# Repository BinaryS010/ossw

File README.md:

# Open SCART SWitch (OSSW)

## Overview

The **Open SCART Switch** (OSSW) is an RGB video and audio SCART switch designed to connect up to **8** RGB capable video game consoles with compatible display devices or scalers such as the **Open Source Scan Converter (OSSC).**

It was designed for use with properly constructed **RGB SCART** cables which correctly attenuate video and sync signals to levels safe for use with consumer grade televisions and the OSSC.

## Motivation

I designed this device to scratch a few itches, but mostly because there are currently no open source SCART switch designs within the retro gaming community.

It would have been cheaper to buy an existing solution, of which there are several very good ones, but I've learnt a lot throughout this project.

## Features

Currently the OSSW has the following features:

 * **8** SCART **inputs**, with **2** SCART **outputs**. Supports simultaneous output (**untested**).
 * Integrated **video amplifier** and switchable **sync stripper.**
 * Support for **Composite sync (CSYNC)**, **Sync-over-composite** or **Sync-on-Luma** on **SCART pin 20.**
 * Backlit LCD character **display** with menu driven interface.
 * Infrared **remote** and **5 button** control interface support.
 * Line-level **stereo audio** output via RCA jacks.
 * Built in 64Kb **EEPROM** to save and load configuration data.
 * Externally powered by **7.5V DC** supply. **2.5mm** barrel jack, centre positive.
 * Power **input polarity** and **over-voltage protection**, with onboard 1A fuse.
 * **SD Card** interface. (**unused/untested**, see future features).
 * Simple **expansion** interface for future feature support (**untested**).
 * Transient voltage **protection** for SCART Input and Outputs (**untested**).

### Limitations

The following are known limitations with the OSSW:

 * **Euro SCART** only. Currently NO support for **JP-21 SCART** standard.
 * Currently, **manual** switching only (see future features below).
 * No **audio amplification** is performed by the OSSW. Audio is currently split between the two SCART outputs and the RCA stereo jacks. A decrease in audio volume may be noticeable when using multiple outputs simultaneously (see future features below).
 * Input and output SCART ports can tolerate a maximum of **5V.** Use properly constructed RGB SCART cables to ensure no signal line (particularly, **SCART pin 8**) carries no more than **5V**.
 * Fimware only upgradeable using compatible programmer, such as an Atmel ICE (see future features).
 * Infrared remote control decoding is currently limited to **NEC protocol** only. Remote specific codes are hard-coded in the firmware.

### Future Features

The following features are planned for the OSSW:

 * Audio amplification.
 * Sync detection and automatic switching funtionality.
 * SD card based firmware upgrades and custom profile loading and saving.
 * Infrared remote control training and additional protocol decoding support.

### Warnings

Currently the device should only be used with **75 ohm** attenuated sync signals. Using the OSSW with **TTL** level sync signals will likely damage upstream devices such as the OSSC.

## Hardware

OSSW hardware overview and build instructions are located in the [HARDWARE](./HARDWARE.md) readme.

## Firmware

OSSW firmware build, programming and debugging instructions are located in the [FIRMWARE](./FIRMWARE.md) readme.

## Usage

OSSW usage instructions are located in the [USAGE](./USAGE.md) readme.

## Revision history

Please see the [CHANGELOG](./CHANGELOG)

## Disclaimer

This is a **DIY hobby** project currently in an early prototype stage. 

I am **not** a trained electrical engineer and although this device seems to work well with my equipment it may not work so well with other setups.

I **do not** intend to sell kits or completed devices. Design files are released to the community in the hope that the design may be improved upon should people wish to contribute. 

I **may** sell surplus PCBs at around cost price (+shipping) but **ONLY** if I have them available.

I offer **NO WARRANTY** of any kind and assume **NO RESPONSIBILITY** for potential damage or loss caused by this device. **Use the information in the repository at your own risk.**

I also offer **NO GUARANTEE** of support if you attempt to build and operate one of these devices. This is a hobby project and not a business. I'm open to contributions and suggestions on current or future features but it's unlikely I'll have time to answer direct queries.

## Donations

Donations are certainly not expected or required. However, if you would like to contribute a small donation towards future revisions of this project then please use one of the methods below:

 * Paypal: **ossw AT binarysolo.co.uk** (replace AT with @).
 * Bitcoin: **36CN15aT6YL5B6MN5kqg4JD5AhEYchCwxG**

Any and all donations are greatly appreciated.

## License

This project is licensed under the GNU General Public License, version 3 (GPLv3).

## Copyright

The **Open Scart Switch (OSSW)** project is Copyright(c) 2019-2021 Binary Solo.

Elements of the OSSW project that are derived from other works are credited within the relevant source files. Those works are copyright of their respective owners as indicated in the original copyright notice.

## Contact

The OSSW developer can be contacted via email as **ossw AT binarysolo.co.uk** (replace the AT with @).

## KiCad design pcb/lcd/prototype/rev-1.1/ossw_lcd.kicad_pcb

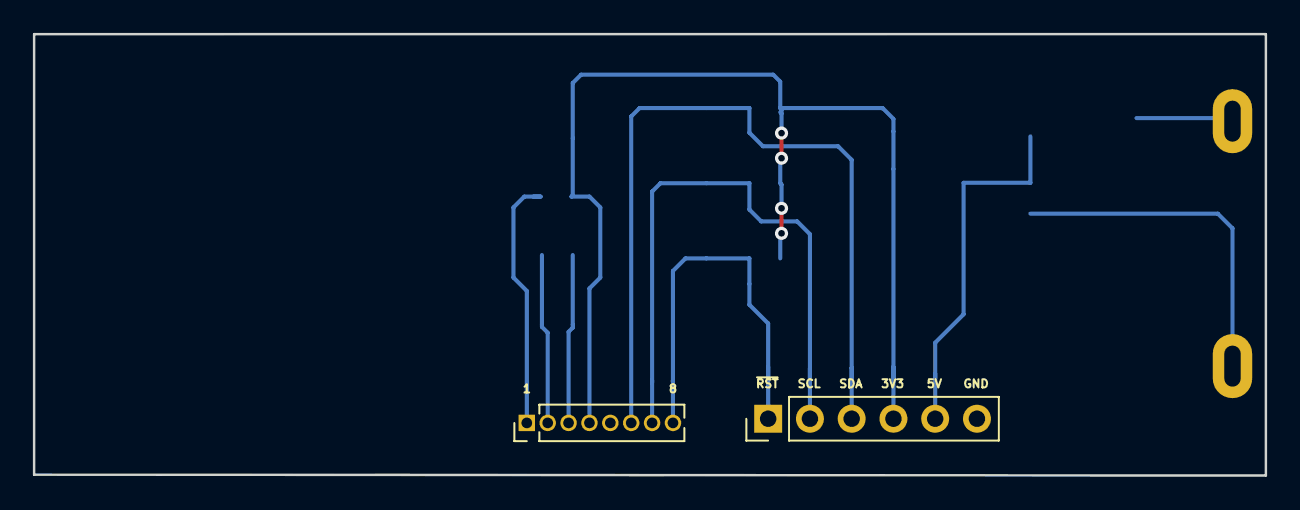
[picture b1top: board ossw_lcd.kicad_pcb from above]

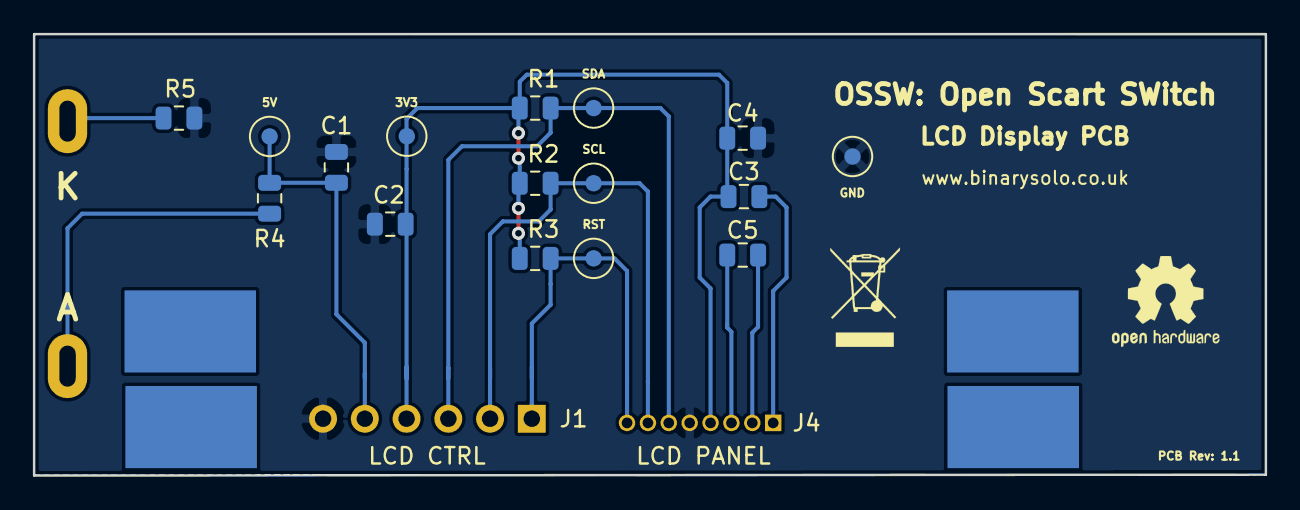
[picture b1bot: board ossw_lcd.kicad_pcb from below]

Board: 2 copper layers, 74.9 x 26.8 mm, 23 parts (21 on the bottom side), 11 nets.

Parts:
3V3, 5V: TestPoint; TestPoint_Pad_D2.0mm
C1, C2, C3, C4, C5: 1uF; C_0805_2012Metric
GND: TestPoint; TestPoint_Pad_D2.0mm
J1: LCD CTRL; PinHeader_1x06_P2.54mm_Vertical
J2: LCD BL; lcd_backlight
J3: ANCHOR 1; anchor
J4: LCD PANEL; PinHeader_1x08_P1.27mm_Vertical
J5: ANCHOR 2; anchor
J6: ANCHOR 3; anchor
J7: ANCHOR 4; anchor
R1, R2, R3: 4K7; R_0805_2012Metric
R4: 47R; R_0805_2012Metric
R5: 0R; R_0805_2012Metric
RST: TestPoint; TestPoint_Pad_D2.0mm
SCL: TestPoint; TestPoint_Pad_D2.0mm
SDA: TestPoint; TestPoint_Pad_D2.0mm

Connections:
3V3: 3V3.1, C2.1, C3.2, C4.1, J1.4, J4.4, R1.2, R2.2, R3.2
5V: 5V.1, C1.1, J1.5, R4.2
GND: C1.2, C2.2, C4.2, GND.1, J1.6, J4.5, R5.2
unnamed: C3.1, J4.1
unnamed: C5.1, J4.2
unnamed: C5.2, J4.3
unnamed: J2.1, R4.1
unnamed: J2.2, R5.1
RST: J1.1, J4.8, R3.1, RST.1
SCL: J1.2, J4.7, R2.1, SCL.1
SDA: J1.3, J4.6, R1.1, SDA.1

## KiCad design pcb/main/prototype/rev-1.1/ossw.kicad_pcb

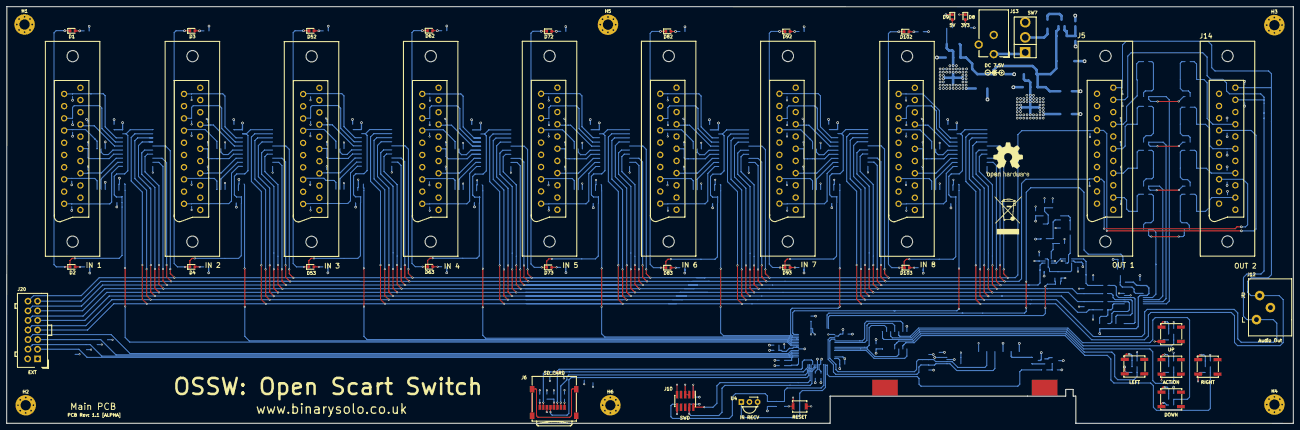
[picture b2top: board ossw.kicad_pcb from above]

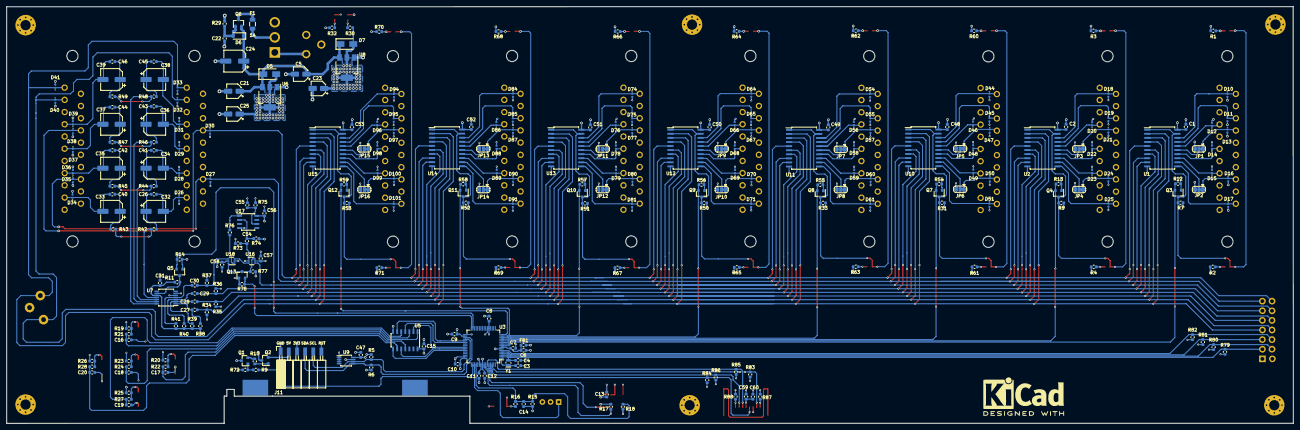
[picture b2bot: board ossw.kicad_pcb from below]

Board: 4 copper layers, 401.5 x 130.1 mm, 332 parts (283 on the bottom side), 207 nets.

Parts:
C1, C2, C7, C8, C9, C10, C12, C13, C15, C16, C17, C18, C19, C20, C26, C31, C40, C41, C42, C43, C44, C45, C46, C47, C48, C49, C50, C51, C52, C53, C56, C57, C58, C59: 0.1uF; C_0603_1608Metric
C3, C4: 6.4pF; C_0603_1608Metric
C5, C21, C23, C25: 10uF; CP_Elec_4x5.4
C6, C60: 10uF; C_0603_1608Metric
C11: 1uF; C_0603_1608Metric
C14: 100pF; C_0603_1608Metric
C22: 15nF/50V; C_0603_1608Metric
C24: 47uF; CP_Elec_6.3x5.4
C27, C28, C29, C30, C54, C55: 100nF; C_0603_1608Metric
C32, C33, C34, C35, C36, C37, C38, C39: 220uF; CP_Elec_6.3x7.7
D1, D2, D3, D4, D52, D53, D62, D63, D72, D73, D82, D83, D92, D93, D102, D103: LED_Small; LED_0603_1608Metric
D5, D7: 1N4002; D_SMA
D6: 10V; D_SOD-123
D8: 3V3; LED_0603_1608Metric
D9: 5V; LED_0603_1608Metric
D10, D11, D12, D13, D14, D15, D16, D17, D18, D19, D20, D21, D22, D23, D24, D25, D26, D27, D28, D29, D30, D31, D32, D33, D34, D35, D36, D37, D38, D39, D40, D41, D44, D45, D46, D47, D48, D49, D50, D51, D54, D55, D56, D57, D58, D59, D60, D61, D64, D65, D66, D67, D68, D69, D70, D71, D74, D75, D76, D77, D78, D79, D80, D81, D84, D85, D86, D87, D88, D89, D90, D91, D94, D95, D96, D97, D98, D99, D100, D101: D_TVS; D_0402_1005Metric
F1: 1A; Fuse_1206_3216Metric
FB1: BLM21PG331SN1; L_0603_1608Metric
H1, H2, H3, H4, H5, H6: MountingHole; MountingHole_3.2mm_M3_Pad_Via
J1: IN 1; SCART_Female
J2: IN 3; SCART_Female
J3: IN 2; SCART_Female
J4: IN 4; SCART_Female
J5: OUT 1; SCART_Female
J6: SD_CARD; microSD_HC_Wuerth_693072010801
J7: IN 5; SCART_Female
J8: IN 6; SCART_Female
J9: IN 7; SCART_Female
J10: SWD; PinHeader_2x05_P1.27mm_Vertical_SMD
J11: LCD; Socket_Strip_Angled_1x06_Pitch2.54mm
J12: Audio Out; PSG01550
J13: DC 7.5V; BarrelJack_FC681465P
J14: OUT 2; SCART_Female
J15: IN 8; SCART_Female
J16: A1; anchor
J17: A2; anchor
J18: A3; anchor
J19: A4; anchor
J20: EXT; TE_MATE-N-LOK_4-794630-4_2x07_P3.0mm_Vertical
JP1: FUNC1; SolderJumper-3_P1.3mm_Bridged12_RoundedPad1.0x1.5mm
JP2: BLANK1; SolderJumper-3_P1.3mm_Bridged12_RoundedPad1.0x1.5mm
JP3: FUNC2; SolderJumper-3_P1.3mm_Bridged12_RoundedPad1.0x1.5mm
JP4: BLANK2; SolderJumper-3_P1.3mm_Bridged12_RoundedPad1.0x1.5mm
JP5: FUNC3; SolderJumper-3_P1.3mm_Bridged12_RoundedPad1.0x1.5mm
JP6: BLANK3; SolderJumper-3_P1.3mm_Bridged12_RoundedPad1.0x1.5mm
JP7: FUNC4; SolderJumper-3_P1.3mm_Bridged12_RoundedPad1.0x1.5mm
JP8: BLANK4; SolderJumper-3_P1.3mm_Bridged12_RoundedPad1.0x1.5mm
JP9: FUNC5; SolderJumper-3_P1.3mm_Bridged12_RoundedPad1.0x1.5mm
JP10: BLANK5; SolderJumper-3_P1.3mm_Bridged12_RoundedPad1.0x1.5mm
JP11: FUNC6; SolderJumper-3_P1.3mm_Bridged12_RoundedPad1.0x1.5mm
JP12: BLANK6; SolderJumper-3_P1.3mm_Bridged12_RoundedPad1.0x1.5mm
JP13: FUNC7; SolderJumper-3_P1.3mm_Bridged12_RoundedPad1.0x1.5mm
JP14: BLANK7; SolderJumper-3_P1.3mm_Bridged12_RoundedPad1.0x1.5mm
JP15: FUNC8; SolderJumper-3_P1.3mm_Bridged12_RoundedPad1.0x1.5mm
JP16: BLANK8; SolderJumper-3_P1.3mm_Bridged12_RoundedPad1.0x1.5mm
Q1: BC847; SOT-23
Q2: BC857; SOT-23
Q3, Q4, Q5, Q7, Q8, Q9, Q10, Q11, Q12, Q13: BSS138; SOT-23
Q6: SI2399; SOT-23
R1, R2, R3, R4, R60, R61, R62, R63, R64, R65, R66, R67, R68, R69, R70, R71: 220R; R_0603_1608Metric
R5, R6: 4K7; R_0603_1608Metric
R7, R8, R11, R12, R13, R14, R19, R20, R21, R22, R23, R24, R25, R26, R27, R28, R31, R33, R50, R51, R52, R53, R54, R55, R56, R57, R58, R59, R72, R77, R78, R83, R84, R85, R86, R87, R88: 10K; R_0603_1608Metric
R9, R10, R17: 1K; R_0603_1608Metric
R15, R79, R80, R81, R82: 2K2; R_0603_1608Metric
R16: 330R; R_0603_1608Metric
R18: 39R; R_0603_1608Metric
R29: 12K; R_0603_1608Metric
R30: 150R; R_0603_1608Metric
R32, R34, R35, R36, R37, R42, R43, R44, R45, R46, R47, R48, R49, R73: 75R; R_0603_1608Metric
R38, R39, R40, R41, R74: 5.6M; R_0603_1608Metric
R75: 680K; R_0603_1608Metric
R76: 470R; R_0603_1608Metric
SW1: RESET; MPTFP2-Q-TR
SW2: UP; LTL-613R-V-TR
SW3: LEFT; LTL-613R-V-TR
SW4: ACTION; LTL-613R-V-TR
SW5: DOWN; LTL-613R-V-TR
SW6: RIGHT; LTL-613R-V-TR
SW7: SW_SPST; SW_SPDT
U1, U2, U10, U11, U12, U13, U14, U15: SN74CBT3244; SOIC-20W_7.5x12.8mm_P1.27mm
U3: ATSAMD21J18A-AUT; TQFP-64_10x10mm_P0.5mm
U4: IR RECV; Vishay_MINICAST-3Pin
U5: 74HC14; SOIC-14_3.9x8.7mm_P1.27mm
U6: NCP1117ST33T3G; SOT-223
U7: THS7374; TSSOP-14_4.4x5mm_P0.65mm
U8: NCP1117ST50T3G; SOT-223
U9: 24LC64; MSOP-8_3x3mm_P0.65mm
U16, U18: TS5A3159DCK; SOT-363_SC-70-6
U17: LM1881; SOIC-8_3.9x4.9mm_P1.27mm
Y1: 32.768kHz; Crystal_SMD_MicroCrystal_CC8V-T1A-2Pin_2.0x1.2mm

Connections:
+3V3: C8.1, C9.1, C10.1, C12.1, C13.2, C14.1, C15.1, C25.1, C47.2, C59.2, C60.2, D5.2, FB1.2, J6.4, J10.1, J11.1, J11.4, Q3.1, Q4.1, Q5.1, Q7.1, Q8.1, Q9.1, Q10.1, Q11.1, Q12.1, Q13.1, R5.2, R6.2, R12.2, R13.2, R14.2, R15.1, R17.2, R19.1, R20.1, R23.1, R25.1, R26.1, R32.1, R54.2, R55.2, R56.2, R57.2, R58.2, R59.2, R78.2, R83.2, R84.2, R85.2, R86.2, R87.2, R88.2, U3.21, U3.34, U3.48, U3.56, U4.3, U5.14, U6.2, U6.4, U9.8
+5V: C1.2, C2.2, C23.1, C31.2, C48.2, C49.2, C50.2, C51.2, C52.2, C53.2, C56.2, C57.2, C58.2, D7.2, J20.1, Q2.3, R1.1, R2.1, R3.1, R4.1, R7.2, R8.2, R11.2, R30.1, R31.2, R33.2, R38.1, R39.1, R40.1, R41.1, R50.2, R51.2, R52.2, R53.2, R60.1, R61.1, R62.1, R63.1, R64.1, R65.1, R66.1, R67.1, R68.1, R69.1, R70.1, R71.1, R74.1, R77.2, U1.20, U2.20, U7.10, U8.2, U8.4, U10.20, U11.20, U12.20, U13.20, U14.20, U15.20, U16.5, U17.8, U18.5
+7.5V: C5.1, C21.1, C24.1, D5.1, D6.1, D7.1, Q6.2, U6.3, U8.3
/Audio Amplifier/AUDIO_AMP1: D32.1, D40.1, J5.3, J12.3, J14.3, J20.8, U1.3, U2.3, U10.3, U11.3, U12.3, U13.3, U14.3, U15.3
/Audio Amplifier/AUDIO_AMP2: D33.1, D41.1, J5.1, J12.2, J14.1, J20.7, U1.2, U2.2, U10.2, U11.2, U12.2, U13.2, U14.2, U15.2
/MCU/BTN_A: U3.41, U5.2
/MCU/BTN_D: U3.37, U5.6
/MCU/BTN_L: U3.42, U5.10
/MCU/BTN_R: U3.43, U5.8
/MCU/BTN_U: U3.38, U5.4
/MCU/BYPASS: Q5.2, R14.1, U3.31
/MCU/EXT_CTRL1: J20.3, R79.2, U3.3
/MCU/EXT_CTRL2: J20.4, R80.2, U3.4
/MCU/EXT_CTRL3: J20.5, R81.2, U3.5
/MCU/EXT_CTRL4: J20.6, R82.2, U3.6
/MCU/I2C_SCL: J11.2, R5.1, U3.36, U9.6
/MCU/I2C_SDA: J11.3, R6.1, U3.35, U9.5
/MCU/IR_RECV: U3.51, U4.1
/MCU/LCD_BL: R9.2, U3.50
/MCU/SD_MISO: J6.7, R83.1, U3.62
/MCU/SD_MOSI: J6.3, R85.1, U3.59
/MCU/SD_SCK: J6.5, R84.1, U3.60
/MCU/SWCLK: J10.4, R17.1, U3.57
/MCU/SWDIO: J10.2, U3.58
/MCU/SYNC_SPLIT: Q13.2, R78.1, U3.32
/MCU/VIDEO_CTRL1: Q5.3, R11.1, U7.9
/MCU/VIDEO_CTRL2: Q13.3, R77.1, U16.6, U18.6
/MCU/XIN32: C3.2, U3.1, Y1.1
/MCU/XOUT32: C4.2, U3.2, Y1.2
/MCU/~BUS_EN1: Q3.2, R12.1, U3.9
/MCU/~BUS_EN2: Q4.2, R13.1, U3.10
/MCU/~BUS_EN3: Q7.2, R54.1, U3.11
/MCU/~BUS_EN4: Q8.2, R55.1, U3.12
/MCU/~BUS_EN5: Q9.2, R56.1, U3.13
/MCU/~BUS_EN6: Q10.2, R57.1, U3.14
/MCU/~BUS_EN7: Q11.2, R58.1, U3.15
/MCU/~BUS_EN8: Q12.2, R59.1, U3.16
/MCU/~BUS_ENABLE1: D1.1, D2.1, Q3.3, R7.1, U1.1, U1.19
/MCU/~BUS_ENABLE2: D3.1, D4.1, Q4.3, R8.1, U2.1, U2.19
/MCU/~BUS_ENABLE3: D52.1, D53.1, Q7.3, R31.1, U10.1, U10.19
/MCU/~BUS_ENABLE4: D62.1, D63.1, Q8.3, R33.1, U11.1, U11.19
/MCU/~BUS_ENABLE5: D72.1, D73.1, Q9.3, R50.1, U12.1, U12.19
/MCU/~BUS_ENABLE6: D82.1, D83.1, Q10.3, R51.1, U13.1, U13.19
/MCU/~BUS_ENABLE7: D92.1, D93.1, Q11.3, R52.1, U14.1, U14.19
/MCU/~BUS_ENABLE8: D102.1, D103.1, Q12.3, R53.1, U15.1, U15.19
/MCU/~RESET: C14.2, R15.2, R16.2, R18.1, U3.52
/MCU/~SD_CS: J6.2, R86.1, U3.61
/SCART Input 1/AL1: D11.1, J1.6, U1.17
/SCART Input 1/AR1: D10.1, J1.2, U1.18
/SCART Input 1/BLANK1: D16.1, J1.16, JP2.1
/SCART Input 1/BLUE1: D12.1, J1.7, U1.16
/SCART Input 1/CSYNC1: D17.1, J1.20, U1.11
/SCART Input 1/FUNC1: D13.1, J1.8, JP1.1
/SCART Input 1/GREEN1: D14.1, J1.11, U1.14
/SCART Input 1/RED1: D15.1, J1.15, U1.13
/SCART Input 1/SCART1_OUT8: D30.1, D38.1, J5.8, J14.8, J20.14, U1.5, U2.5, U10.5, U11.5, U12.5, U13.5, U14.5, U15.5
/SCART Input 1/SCART16: D27.1, D35.1, J5.16, J14.16, J20.13, U1.8, U2.8, U10.8, U11.8, U12.8, U13.8, U14.8, U15.8
/SCART Input 1/VIDEO_AMP1: C27.2, J20.9, R34.1, U1.4, U2.4, U10.4, U11.4, U12.4, U13.4, U14.4, U15.4
/SCART Input 1/VIDEO_AMP2: C28.2, J20.10, R35.1, U1.6, U2.6, U10.6, U11.6, U12.6, U13.6, U14.6, U15.6
/SCART Input 1/VIDEO_AMP3: C29.2, J20.11, R36.1, U1.7, U2.7, U10.7, U11.7, U12.7, U13.7, U14.7, U15.7
/SCART Input 1/VIDEO_AMP4: J20.12, U1.9, U2.9, U10.9, U11.9, U12.9, U13.9, U14.9, U15.9, U16.4
/SCART Input 2/AL2: D19.1, J3.6, U2.17
/SCART Input 2/AR2: D18.1, J3.2, U2.18
/SCART Input 2/BLANK2: D24.1, J3.16, JP4.1
/SCART Input 2/BLUE2: D20.1, J3.7, U2.16
/SCART Input 2/CSYNC2: D25.1, J3.20, U2.11
/SCART Input 2/FUNC2: D21.1, J3.8, JP3.1
/SCART Input 2/GREEN2: D22.1, J3.11, U2.14
/SCART Input 2/RED2: D23.1, J3.15, U2.13
/SCART Input 3/AL3: D45.1, J2.6, U10.17
/SCART Input 3/AR3: D44.1, J2.2, U10.18
/SCART Input 3/BLANK3: D50.1, J2.16, JP6.1
/SCART Input 3/BLUE3: D46.1, J2.7, U10.16
/SCART Input 3/CSYNC3: D51.1, J2.20, U10.11
/SCART Input 3/FUNC3: D47.1, J2.8, JP5.1
/SCART Input 3/GREEN3: D48.1, J2.11, U10.14
/SCART Input 3/RED3: D49.1, J2.15, U10.13
/SCART Input 4/AL4: D55.1, J4.6, U11.17
/SCART Input 4/AR4: D54.1, J4.2, U11.18
/SCART Input 4/BLANK4: D60.1, J4.16, JP8.1
/SCART Input 4/BLUE4: D56.1, J4.7, U11.16
/SCART Input 4/CSYNC4: D61.1, J4.20, U11.11
/SCART Input 4/FUNC4: D57.1, J4.8, JP7.1
/SCART Input 4/GREEN4: D58.1, J4.11, U11.14
/SCART Input 4/RED4: D59.1, J4.15, U11.13
/SCART Input 5/AL5: D65.1, J7.6, U12.17
/SCART Input 5/AR5: D64.1, J7.2, U12.18
/SCART Input 5/BLANK5: D70.1, J7.16, JP10.1
/SCART Input 5/BLUE5: D66.1, J7.7, U12.16
/SCART Input 5/CSYNC5: D71.1, J7.20, U12.11
/SCART Input 5/FUNC5: D67.1, J7.8, JP9.1
/SCART Input 5/GREEN5: D68.1, J7.11, U12.14
/SCART Input 5/RED5: D69.1, J7.15, U12.13
/SCART Input 6/AL6: D75.1, J8.6, U13.17
/SCART Input 6/AR6: D74.1, J8.2, U13.18
/SCART Input 6/BLANK6: D80.1, J8.16, JP12.1
/SCART Input 6/BLUE6: D76.1, J8.7, U13.16
/SCART Input 6/CSYNC6: D81.1, J8.20, U13.11
/SCART Input 6/FUNC6: D77.1, J8.8, JP11.1
/SCART Input 6/GREEN6: D78.1, J8.11, U13.14
/SCART Input 6/RED6: D79.1, J8.15, U13.13
/SCART Input 7/AL7: D85.1, J9.6, U14.17
/SCART Input 7/AR7: D84.1, J9.2, U14.18
/SCART Input 7/BLANK7: D90.1, J9.16, JP14.1
/SCART Input 7/BLUE7: D86.1, J9.7, U14.16
/SCART Input 7/CSYNC7: D91.1, J9.20, U14.11
/SCART Input 7/FUNC7: D87.1, J9.8, JP13.1
/SCART Input 7/GREEN7: D88.1, J9.11, U14.14
/SCART Input 7/RED7: D89.1, J9.15, U14.13
/SCART Input 8/AL8: D95.1, J15.6, U15.17
/SCART Input 8/AR8: D94.1, J15.2, U15.18
/SCART Input 8/BLANK8: D100.1, J15.16, JP16.1
/SCART Input 8/BLUE8: D96.1, J15.7, U15.16
/SCART Input 8/CSYNC8: D101.1, J15.20, U15.11
/SCART Input 8/FUNC8: D97.1, J15.8, JP15.1
/SCART Input 8/GREEN8: D98.1, J15.11, U15.14
/SCART Input 8/RED8: D99.1, J15.15, U15.13
/SCART Output 1/SCART1_OUT7: C38.2, C45.1, D31.1, J5.7
/SCART Output 1/SCART1_OUT11: C36.2, C43.1, D29.1, J5.11
/SCART Output 1/SCART1_OUT15: C34.2, C41.1, D28.1, J5.15
/SCART Output 1/SCART1_OUT19: C26.1, C32.2, D26.1, J5.19
/SCART Output 2/SCART2_OUT7: C39.2, C46.1, D39.1, J14.7
/SCART Output 2/SCART2_OUT11: C37.2, C44.1, D37.1, J14.11
/SCART Output 2/SCART2_OUT15: C35.2, C42.1, D36.1, J14.15
/SCART Output 2/SCART2_OUT19: C33.2, C40.1, D34.1, J14.19
/Video Amplifier/VID_I: C54.2, R73.1, U16.1
/Video Amplifier/VID_O: R76.2, U18.1
GND: C1.1, C2.1, C3.1, C4.1, C5.2, C6.1, C7.1, C8.2, C9.2, C10.2, C11.1, C12.2, C13.1, C15.2, C16.2, C17.2, C18.2, C19.2, C20.2, C21.2, C22.2, C23.2, C24.2, C25.2, C31.1, C47.1, C48.1, C49.1, C50.1, C51.1, C52.1, C53.1, C55.1, C56.1, C57.1, C58.1, C59.1, C60.1, D8.1, D9.1, D10.2, D11.2, D12.2, D13.2, D14.2, D15.2, D16.2, D17.2, D18.2, D19.2, D20.2, D21.2, D22.2, D23.2, D24.2, D25.2, D26.2, D27.2, D28.2, D29.2, D30.2, D31.2, D32.2, D33.2, D34.2, D35.2, D36.2, D37.2, D38.2, D39.2, D40.2, D41.2, D44.2, D45.2, D46.2, D47.2, D48.2, D49.2, D50.2, D51.2, D54.2, D55.2, D56.2, D57.2, D58.2, D59.2, D60.2, D61.2, D64.2, D65.2, D66.2, D67.2, D68.2, D69.2, D70.2, D71.2, D74.2, D75.2, D76.2, D77.2, D78.2, D79.2, D80.2, D81.2, D84.2, D85.2, D86.2, D87.2, D88.2, D89.2, D90.2, D91.2, D94.2, D95.2, D96.2, D97.2, D98.2, D99.2, D100.2, D101.2, H1.1, H2.1, H3.1, H4.1, H5.1, H6.1, J1.4, J1.5, J1.9, J1.13, J1.17, J1.18, J1.21, J2.4, J2.5, J2.9, J2.13, J2.17, J2.18, J2.21, J3.4, J3.5, J3.9, J3.13, J3.17, J3.18, J3.21, J4.4, J4.5, J4.9, J4.13, J4.17, J4.18, J4.21, J5.4, J5.5, J5.9, J5.13, J5.17, J5.18, J5.21, J6.6, J7.4, J7.5, J7.9, J7.13, J7.17, J7.18, J7.21, J8.4, J8.5, J8.9, J8.13, J8.17, J8.18, J8.21, J9.4, J9.5, J9.9, J9.13, J9.17, J9.18, J9.21, J10.3, J10.5, J10.9, J11.6, J12.1, J13.2, J13.3, J14.4, J14.5, J14.9, J14.13, J14.17, J14.18, J14.21, J15.4, J15.5, J15.9, J15.13, J15.17, J15.18, J15.21, J20.2, JP1.3, JP2.3, JP3.3, JP4.3, JP5.3, JP6.3, JP7.3, JP8.3, JP9.3, JP10.3, JP11.3, JP12.3, JP13.3, JP14.3, JP15.3, JP16.3, Q1.3, R29.2, R34.2, R35.2, R36.2, R37.2, R72.1, R73.2, R75.2, R79.1, R80.1, R81.1, R82.1, SW1.2, SW2.1, SW3.1, SW4.1, SW5.1, SW6.1, U1.10, U2.10, U3.7, U3.22, U3.33, U3.47, U3.54, U4.2, U5.7, U6.1, U7.5, U7.6, U8.1, U9.1, U9.2, U9.3, U9.4, U9.7, U10.10, U11.10, U12.10, U13.10, U14.10, U15.10, U16.2, U17.4, U18.2
unnamed: C6.2, C7.2, FB1.1, U3.8
unnamed: C11.2, U3.55
unnamed: C16.1, R21.1, U5.3
unnamed: C17.1, R22.1, U5.11
unnamed: C18.1, R24.1, U5.1
unnamed: C19.1, R27.1, U5.5
unnamed: C20.1, R28.1, U5.9
unnamed: C22.1, D6.2, Q6.1, R29.1
unnamed: C26.2, C32.1, R42.1
unnamed: C27.1, R38.2, U7.1
unnamed: C28.1, R39.2, U7.2
unnamed: C29.1, R40.2, U7.3
unnamed: C30.1, R41.2, U7.4
unnamed: C30.2, R37.1, U18.4
unnamed: C33.1, C40.2, R43.1
unnamed: C34.1, C41.2, R44.1
unnamed: C35.1, C42.2, R45.1
unnamed: C36.1, C43.2, R46.1
unnamed: C37.1, C44.2, R47.1
unnamed: C38.1, C45.2, R48.1
unnamed: C39.1, C46.2, R49.1
unnamed: C54.1, R74.2, U17.2
unnamed: C55.2, R75.1, U17.6
unnamed: D1.2, R1.2
unnamed: D2.2, R2.2
unnamed: D3.2, R3.2
unnamed: D4.2, R4.2
unnamed: D8.2, R32.2
unnamed: D9.2, R30.2
unnamed: D52.2, R60.2
unnamed: D53.2, R61.2
unnamed: D62.2, R62.2
unnamed: D63.2, R63.2
unnamed: D72.2, R64.2
unnamed: D73.2, R65.2
unnamed: D82.2, R66.2
unnamed: D83.2, R67.2
unnamed: D92.2, R68.2
unnamed: D93.2, R69.2
unnamed: D102.2, R70.2
unnamed: D103.2, R71.2
unnamed: F1.1, SW7.2
unnamed: F1.2, Q6.3
unnamed: J6.1, R88.1
unnamed: J6.8, R87.1
unnamed: J10.10, R18.2
unnamed: J11.5, Q2.2
unnamed: J13.1, SW7.1
unnamed: JP1.2, U1.15
unnamed: JP2.2, U1.12
unnamed: JP3.2, U2.15
unnamed: JP4.2, U2.12
unnamed: JP5.2, U10.15
unnamed: JP6.2, U10.12
unnamed: JP7.2, U11.15
unnamed: JP8.2, U11.12
unnamed: JP9.2, U12.15
unnamed: JP10.2, U12.12
unnamed: JP11.2, U13.15
unnamed: JP12.2, U13.12
unnamed: JP13.2, U14.15
unnamed: JP14.2, U14.12
unnamed: JP15.2, U15.15
unnamed: JP16.2, U15.12
unnamed: Q1.1, R9.1, R72.2
unnamed: Q1.2, R10.2
unnamed: Q2.1, R10.1
unnamed: R16.1, SW1.1
unnamed: R19.2, R21.2, SW2.2
unnamed: R20.2, R22.2, SW3.2
unnamed: R23.2, R24.2, SW4.2
unnamed: R25.2, R27.2, SW5.2
unnamed: R26.2, R28.2, SW6.2
unnamed: R42.2, R43.2, U7.11
unnamed: R44.2, R45.2, U7.12
unnamed: R46.2, R47.2, U7.13
unnamed: R48.2, R49.2, U7.14
unnamed: R76.1, U17.1
unnamed: U16.3, U18.3

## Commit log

2021-02-09 Initial commit.
